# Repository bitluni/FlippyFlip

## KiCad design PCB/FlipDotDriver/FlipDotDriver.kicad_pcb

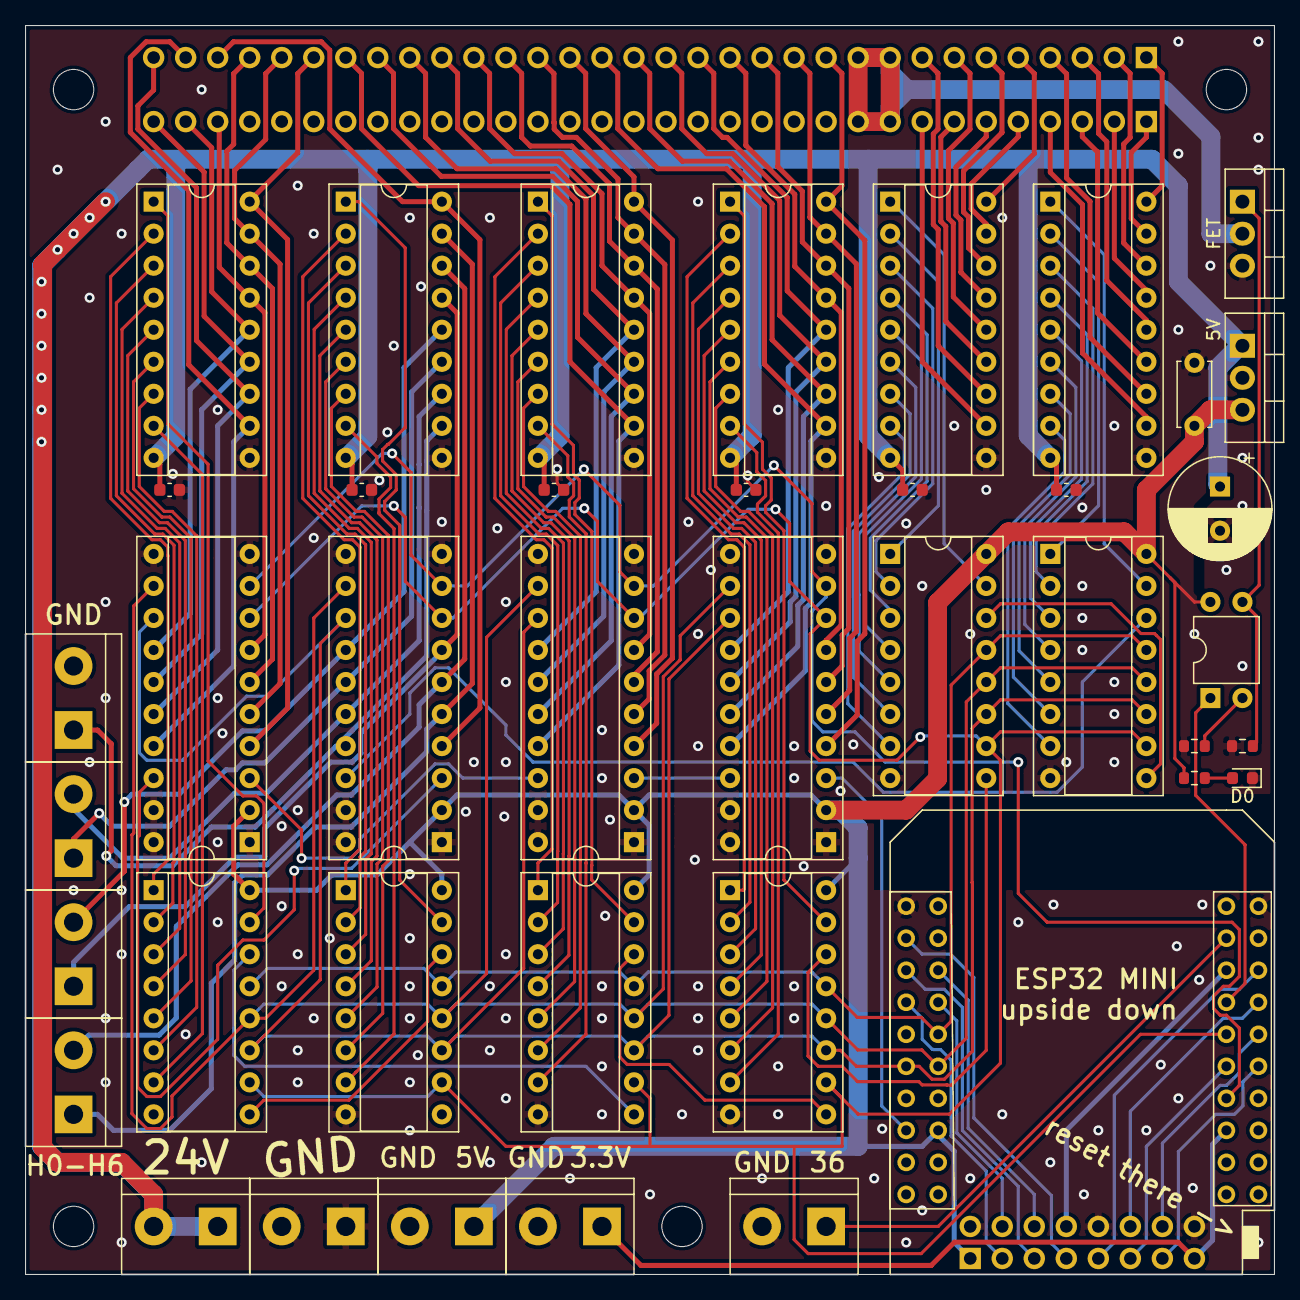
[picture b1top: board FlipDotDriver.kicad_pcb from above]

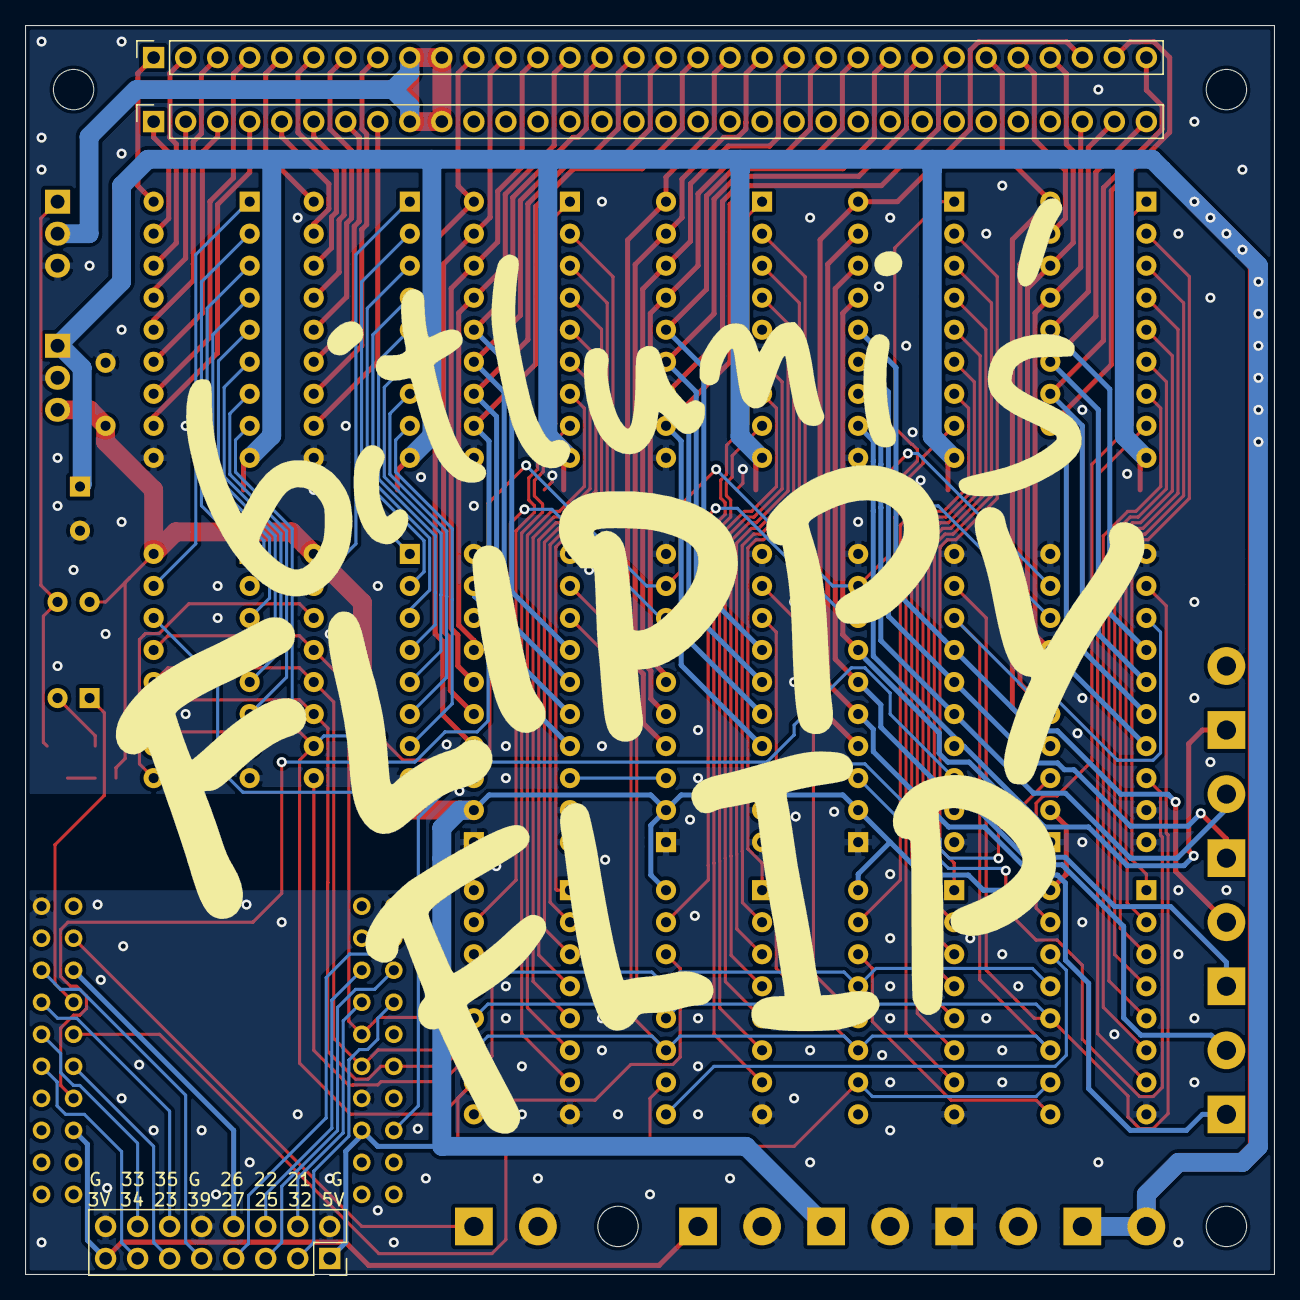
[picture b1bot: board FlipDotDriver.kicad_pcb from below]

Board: 2 copper layers, 99.1 x 99.1 mm, 44 parts (4 on the bottom side), 132 nets.

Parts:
C0, C1, C2, C3, C4, C5: 10uF; C_0603_1608Metric
C6: CP; CP_Radial_D8.0mm_P3.50mm
C7: C; C_Disc_D5.0mm_W2.5mm_P5.00mm
D0: LED; LED_0603_1608Metric
J0, J1: Conn_01x32_Female; PinSocket_1x32_P2.54mm_Vertical
J2: Conn_01x16_Female; PinSocket_2x08_P2.54mm_Vertical
J3, J4, J5, J6, J7, J8, J9, J10, J11: Screw_Terminal_01x02; TerminalBlock_bornier-2_P5.08mm
Q1: IRLZ44N; TO-220-3_Vertical
R0, R1, R2: 1000R; R_0603_1608Metric
U0, U1, U2, U3, U4, U5: TBD62783A; DIP-18_W7.62mm_Socket
U6, U7, U8, U9: TPIC6B595N; DIP-20_W7.62mm_Socket
U10: mini_esp32; ESP32_mini
U11: PC817; DIP-4_W7.62mm
U12: LM7805_TO220; TO-220-3_Vertical
U13, U14, U15, U16, U17, U18: 74HC595; DIP-16_W7.62mm_Socket

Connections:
+3V3: J2.15, J4.1, U10.16
+5V: C7.1, J2.1, J10.1, R0.1, U6.2, U7.2, U8.2, U9.2, U10.35, U11.4, U12.3, U13.16, U14.16, U15.16, U16.16, U17.16, U18.16
+24V: C0.1, C1.1, C2.1, C3.1, C4.1, C5.1, C6.1, J5.1, J5.2, U0.9, U1.9, U2.9, U3.9, U4.9, U5.9, U12.1
/21: J2.4, U10.27
/22: J2.6, U10.25
/23: J2.11, U10.12
/25: J2.5, U10.26
/26: J2.8, U10.6
/27: J2.7, U10.24
/32: J2.3, U10.28
/33: J2.14, U10.9
/34: J2.13, U10.11
/35: J2.12, U10.7
/36: J11.1, U10.4
/39: J2.9, U10.5
/C0: J0.11, U0.18, U9.4
/C1: J0.12, U0.17, U9.5
/C2: J0.13, U0.16, U9.6
/C3: J0.14, U0.15, U9.7
/C4: J0.15, U0.14, U9.14
/C5: J0.16, U0.13, U9.15
/C6: J0.17, U0.12, U9.16
/C7: J0.18, U0.11, U9.17
/C8: J0.19, U1.18, U8.4
/C9: J0.20, U1.17, U8.5
/C10: J0.21, U1.16, U8.6
/C11: J0.22, U1.15, U8.7
/C12: J0.23, U1.14, U8.14
/C13: J0.24, U1.13, U8.15
/C14: J0.25, U1.12, U8.16
/C15: J0.26, U1.11, U8.17
/C16: J0.27, U2.18, U7.4
/C17: J0.28, U2.17, U7.5
/C18: J0.29, U2.16, U7.6
/C19: J1.30, U2.15, U7.7
/C20: J1.31, U2.14, U7.14
/C21: J1.32, U2.13, U7.15
/C22: J0.32, U2.12, U7.16
/C23: J0.31, U2.11, U7.17
/C24: J0.30, U3.18, U6.4
/H0: J6.1, U3.17, U6.5
/H1: J6.2, U3.16, U6.6
/H2: J7.1, U3.15, U6.7
/H3: J7.2, U3.14, U6.14
/H4: J8.1, U3.13, U6.15
/H5: J8.2, U3.12, U6.16
/H6: J9.1, U3.11, U6.17
/OE0: U6.9, U7.9, U8.9, U9.9, U10.14
/OE1: U10.29, U13.13, U14.13, U15.13, U16.13, U17.13, U18.13
/R0: J0.1, U4.18
/R1: J1.1, U4.17
/R2: J0.2, U4.16
/R3: J1.2, U4.15
/R4: J0.3, U4.14
/R5: J1.3, U4.13
/R6: J0.4, U4.12
/R7: J1.4, U4.11
/R8: J0.5, U5.18
/R9: J1.5, U5.17
/R10: J0.6, U5.16
/R11: J1.6, U5.15
/R12: J0.7, U5.14
/R13: J1.7, U5.13
/R14: J0.8, U5.12
/R15: J1.8, U5.11
/RCK: U6.12, U7.12, U8.12, U9.12, U10.31, U13.12, U14.12, U15.12, U16.12, U17.12, U18.12
/RST: U10.8, U11.1
/RSTH: J0.9, J0.10, J1.9, J1.10, Q1.2
/SC0: U0.1, U14.15
/SC1: U0.2, U14.1
/SC2: U0.3, U14.2
/SC3: U0.4, U14.3
/SC4: U0.5, U14.4
/SC5: U0.6, U14.5
/SC6: U0.7, U14.6
/SC7: U0.8, U14.7
/SC8: U1.1, U17.15
/SC9: U1.2, U17.1
/SC10: U1.3, U17.2
/SC11: U1.4, U17.3
/SC12: U1.5, U17.4
/SC13: U1.6, U17.5
/SC14: U1.7, U17.6
/SC15: U1.8, U17.7
/SC16: U2.1, U15.15
/SC17: U2.2, U15.1
/SC18: U2.3, U15.2
/SC19: U2.4, U15.3
/SC20: U2.5, U15.4
/SC21: U2.6, U15.5
/SC22: U2.7, U15.6
/SC23: U2.8, U15.7
/SC24: U3.1, U18.15
/SERIN: U9.3, U10.36
/SH0: U3.2, U18.1
/SH1: U3.3, U18.2
/SH2: U3.4, U18.3
/SH3: U3.5, U18.4
/SH4: U3.6, U18.5
/SH5: U3.7, U18.6
/SH6: U3.8, U18.7
/SR0: U4.1, U13.15
/SR1: U4.2, U13.1
/SR2: U4.3, U13.2
/SR3: U4.4, U13.3
/SR4: U4.5, U13.4
/SR5: U4.6, U13.5
/SR6: U4.7, U13.6
/SR7: U4.8, U13.7
/SR8: U5.1, U16.15
/SR9: U5.2, U16.1
/SR10: U5.3, U16.2
/SR11: U5.4, U16.3
/SR12: U5.5, U16.4
/SR13: U5.6, U16.5
/SR14: U5.7, U16.6
/SR15: U5.8, U16.7
/SRCK: U6.13, U7.13, U8.13, U9.13, U10.32, U13.11, U14.11, U15.11, U16.11, U17.11, U18.11
/SRCLR: U6.8, U7.8, U8.8, U9.8, U10.10, U13.10, U14.10, U15.10, U16.10, U17.10, U18.10
GND: C0.2, C1.2, C2.2, C3.2, C4.2, C5.2, C6.2, C7.2, D0.1, J2.2, J2.10, J2.16, J3.1, J3.2, J4.2, J9.2, J10.2, J11.2, Q1.3, R1.2, R2.2, U0.10, U1.10, U2.10, U3.10, U4.10, U5.10, U6.1, U6.10, U6.11, U6.19, U6.20, U7.1, U7.10, U7.11, U7.19, U7.20, U8.1, U8.10, U8.11, U8.19, U8.20, U9.1, U9.10, U9.11, U9.19, U9.20, U10.1, U10.22, U10.33, U12.2, U13.8, U14.8, U15.8, U16.8, U17.8, U18.8
unnamed: D0.2, R0.2
unnamed: Q1.1, R2.1, U11.3
unnamed: R1.1, U11.2
unnamed: U6.3, U7.18
unnamed: U7.3, U8.18
unnamed: U8.3, U9.18
unnamed: U13.9, U16.14
unnamed: U6.18, U13.14
unnamed: U14.9, U17.14
unnamed: U14.14, U16.9
unnamed: U15.9, U18.14
unnamed: U15.14, U17.9

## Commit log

2021-11-06 Design files added
